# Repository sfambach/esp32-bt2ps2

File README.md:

1/9/24: Serial Mouse support is out for v0.7! Check notes on [release](https://github.com/Hamberthm/esp32-bt2ps2/releases)

24/8/24: Mouse and Multimedia Key support is out for v0.6! Check notes on release

Tested Bluetooth Keyboards and Mice (Please add your own!): [Excel spreadsheet](https://1drv.ms/x/c/496a36eb8f7bab52/EVKre4_rNmoggEllRQIAAAABdvU2lrtNIQN1tRJOs5V3sw?e=jx4JUH)

FreeRTOS ticking rate of 1000hz and other configs are critical. Be sure to use the default SDKconfig.defaults file included!

# ESP32 Bluetooth/BLE to PS/2 keyboard/mouse adapter

## Hardware (this fork)

This fork adds **carrier boards** for the adapter in [`hardware/`](hardware/README.md), each with level shifters and a
4-pin connector for a PS/2 or AT keyboard cable. KiCad 10 files, Gerbers for JLCPCB, schematics and bills of
materials are included.

- **Version 2 (current, [`hardware/v2/`](hardware/v2/README.md)):** SMD board with a soldered-on *ESP32-WROOM-32E*,
  and two through-hole boards, one for a plugged-in *D1 mini ESP32* and one for a soldered-on WROOM; all with
  auto-reset or USB for flashing. **Not manufactured yet.**
- **Version 1 ([`hardware/v1/`](hardware/v1/README.md)):** SMD and THT board, **built and tested**. Gerbers as
  manufactured on the [release v0.1](https://github.com/sfambach/esp32-bt2ps2/releases/tag/v0.1).

| V2 SMD | V2 THT D1 mini | V2 THT WROOM |
|---|---|---|
|  |  |  |

Project to adapt a Bluetooth or BLE keyboard and/or mouse to use on a computer with compatible PS/2 keyboard/mouse connector/s, wirelessly.
Note that big DIN 5 pin connectors ("AT" keyboard) and Mini-DINs (the violet ones) are equally supported.

YouTube demo: https://youtu.be/2PVjWfAAJFE

# Compatibility

Tested Bluetooth Keyboards and Mice (Please add your own!): https://1drv.ms/x/s!AlKre4_rNmpJiYpl1v4KcbK1Pm77zA?e=0I6QRB

Builds with ESP-IDF v5.3.0 and v6.1.0 (both build-tested in this fork; v5.3.3 up to v5.x was reported NOT working upstream and is untested here), compiled on Visual Studio Code. Multi-device support may not work on lower versions of the SDK.

**Developed and tested on the ESP32 DevKit rev 1 board, other variants may not work!**

WARNING: This project is for use in a plain ESP-32 module with BLE and BT Classic support and dual core processor. If you have another variant like C3, you'll have to adapt the code.

* ESP32 S3/C3 (BLE only boards): Check https://github.com/Hamberthm/esp32-bt2ps2/issues/3
* USB-HID instead of PS/2: Check https://github.com/Hamberthm/esp32-bt2ps2/issues/4

# Electrical connections

DIN and Mini-DIN connectors have similar pinout but in different arrangements.

Please use a multimeter and online info to make your cable. Beware of voltage present on the port, you can short and fry things!

Connections:

| ESP32 pin | PS/2 pin | example color | Notes                              |
| --------- | -------- | ------------- |  --------------------------------- |
| 23 or any | DATA     | orange        | Repeat on other pin for mouse bus  |
| 22 or any | CLK      | white         | Repeat on other pin for mouse bus  |
| GND       | GND      | black         | Always connect!                    |
| Vin       | +5v      | red           | Disconnect if using USB power!     |

You can change the DATA and CLK pins to whatever suits your fancy using these lines in the main.cpp file:

```cpp
const int KB_CLK_PIN = 22;
const int KB_DATA_PIN = 23;

const int MOUSE_CLK_PIN = 26;
const int MOUSE_DATA_PIN = 25;
```
Note: Pin 12 & 13 are ideal to solder a connector so you can use Vin, GND, 13 and 12 all in a row (ESP32 DevKit rev 1 boards). BEWARE that pin 12 is a strapping pin on the ESP32 and the module will FAIL to boot due to high signals from the PS/2 port. You can remove the strapping function of pin 12 by blowing an [eFuse](https://docs.espressif.com/projects/esptool/en/latest/esp32s2/espefuse/index.html) on your board. Use the following command:

```
python espefuse.py --port COM4 set_flash_voltage 3.3V
```

Also, applying voltage to pins 1 & 3 (U0 TXD and RXD) could cause the serial communication not to work, thus making serial console output impossible. Be careful on the ones you choose!

There is no need to connect the 5 volts from the port if you wish to power the board over USB. For debugging I recommend you leave it disconnected, as you can end up back-feeding 5 volts back to the PS/2 port, bad things can happen. Once all is working and you don't want to debug anymore, the 5 volts from the port are enough to power the board over the Vin (regulated) pin, making this a pretty neat standalone device!

NOTE: Don't leave the GND cable from the PS2 port floating, otherwise communication won't work! Always connect GND cable to the board even if you're using external power.

Note: ESP32 is **unofficially** 5V tolerant, so you can directly connect PS/2 pins to the board, that's my setup on my rev v1 board and I had no problems. However, you may use a logic level converter.

# Building and flashing

*Note there's a binary release available!

Project works as-is under Visual Studio Code (2024). You need to have the Espressif IDF extension installed and ESP-IDF v5.3.0 or v6.1.0 (build-tested). Workflow is as follows:

1- Install Visual Studio Code

2- On the left, open the extensions panel

3- Search and install the Espressif IDF extension

4- Open the command prompt pressing Ctrl+Shift+P

5- Execute command "ESP-IDF: Configure ESP-IDF extension"

6- Select Express, and under "Select ESP-IDF version" choose v5.3.0 or v6.1.0 (v5.3.3 up to v5.x reported NOT working upstream, untested here)

7- After installation, select File > Open Folder and open the ESP32-BT2PS2 project folder

8- Start building by pressing Ctrl+E and then B, or using the Build button in the bottom bar

9- If succesfully built, connect and flash your ESP32 board (Ctrl+E then F, or the flash button)

Or on the command line (Linux; on Windows use the ESP-IDF installer and `idf.py` in its shell):

```
git clone -b v6.1.0 --recursive https://github.com/espressif/esp-idf.git
cd esp-idf && ./install.sh esp32 && . ./export.sh
git clone https://github.com/sfambach/esp32-bt2ps2.git
cd esp32-bt2ps2 && idf.py build
idf.py -p /dev/ttyUSB0 -b 115200 flash monitor
```

Keep the committed `sdkconfig` (1000 Hz FreeRTOS tick, BLE 4.2 API enabled).

Refer to the following link for more instructions:

* https://github.com/espressif/vscode-esp-idf-extension/blob/master/docs/tutorial/install.md

Once succesfully built and flashed, you're ready to rock! (your BLE keyboard on an ancient computer, that is).

## Known problems (this fork)

**Build failed with ESP-IDF 6.x (fixed).** The linker reported `undefined reference to 'esp_ble_gap_set_scan_params'`, `esp_ble_gap_start_scanning` and `esp_ble_resolve_adv_data`, because the old committed sdkconfig (from v5.3.0) had the legacy BLE 4.2 API disabled. `sdkconfig.defaults` now sets `CONFIG_BT_BLE_42_FEATURES_SUPPORTED=y` and `CONFIG_BT_BLE_42_SCAN_EN=y`, and `sdkconfig` was regenerated with v6.1.0. Build-tested with ESP-IDF v6.1.0 and v5.3.0 (`idf.py fullclean build`); the v6.1 build runs on hardware (ESP32 DevKit, Micro 8088).

**AltGr unreliable, swallowed keys and stuck modifiers on slow hosts (fixed).** Seen on a Micro 8088 (Sergey Kiselev) with DOS 3.31 and KEYB GR, while a real PS/2 keyboard worked. The PS/2 sender in `esp32-ps2dev` dropped the rest of a packet when the host held CLK low for more than 1.5 ms after a byte (e.g. while INT 9 processed `E0`), did not notice when the host aborted a byte mid-transfer, answered Resend (`FE`) with `FA` instead of repeating the last byte, and gave up on a packet when the host wanted to send a command. Lost `E0` bytes turned AltGr into left Alt, and lost break codes left Ctrl/Alt stuck. Now each byte is retried (up to 100 ms) and retransmitted after a host abort or command, Resend repeats the last byte, and there is a 1 ms gap between bytes of a packet (as in HIDman).

**`#` and `<>` missing on German/ISO keyboards.** The ISO keys Non-US # (HID 0x32) and Non-US \ (HID 0x64) had no PS/2 mapping and were dropped. Fixed in this fork (#2): 0x32 sends set-2 code 0x5D, 0x64 sends 0x61.

**Slow BLE reconnect (fixed).** After the keyboard woke up or came back in range it took several seconds to type again. The BLE connection daemon always ran its full 5 s scan before looking for the bonded keyboard, and every reconnect re-read the keyboard's GATT database (`CONFIG_BT_GATTC_CACHE_NVS_FLASH` was off). Now the daemon stops the scan as soon as a bonded device advertises and connects right away, and the GATT cache is on. A monitor log from 31.10.2026 showed the same delay after power-on: the startup pairing scan saw the keyboard at 11.7 s but connected only at 21.7 s, after finishing the 5 s BLE scan and the 5 s BT Classic inquiry. The startup scan now also stops early for a bonded keyboard and skips the BT Classic inquiry then. Confirmed on hardware (01.11.2026, RK-M75 BLE): connected about 1.1 s after the keyboard starts advertising, both after power-on and after the keyboard dropped the link.

# Usage and debugging

Once powered up and first of all, the code will create and init an `esp32_ps2dev::PS2Keyboard` object, so it can start to talk to the computer as soon as possible. This is critical because during boot the BIOS can send different commands to the module to test the presence of the keyboard.

After PS/2 init, the module scans for nearby Bluetooth and BLE devices. If the last bonded keyboard is in range, it will try to connect to it using the keys stored on the NVS flash, so no pairing is needed for every connection. If it doesn't detect a previously bonded device, it will try to connect to the nearest keyboard in pairing mode. If both processes fail, it will wait one second and scan again until it finds anything.

IMPORTANT: Is recommended to do the pairing to the keyboard BEFORE connecing the board to a PS/2 port. For this, connect a charger or power bank to the ESP's USB port and pair your device more comfortably.

For v0.6, you can invoke pairing during execution (blue LED on) at any time. Press the "BOOT" button on the rev v1 board, essentially shorting GPIO_0 to ground. LED will go off and enter pairing mode. To cancel pairing, press and hold for 3 seconds (pairing aborting does not work on startup pairing).

**LED off: Pairing mode activated. LED on: normal execution, only previously paired devices can connect at any time.**

### >> BLE KEYBOARD OR MOUSE PAIRING: 
Set keyboard or mouse in pairing mode and power on the board. No code entry required.

### >> BLUETOOTH CLASSIC KEYBOARD PAIRING (code pairing):

1- Set keyboard in pairing mode and power on the board.

2- Wait until you see a short blast of quick flashes, then pay attention:

3- For each code digit, the board will flash the LED the number of times equal to the digit.

4- Press each digit on the keyboard as you read them (do not wait until it finishes! Some keyboards have a timeout).

5- If the digit is 0, a steady light will show for 1.5 seconds instead of the digit.

6- When you see the blast of quick flashes again, press ENTER.

OR you can always look at the code using the Serial monitor console, whatever you find easier, you fancy boy.

### >> BLUETOOTH CLASSIC KEYBOARD PAIRING, LEGACY PROCEDURE (legacy code pairing):

In older keyboards, the user must enter a custom code on the host device and then on the keyboard. Since we can't input it easily on the ESP32, the code is fixed to 1234.

1- Set keyboard in pairing mode and power on the board

2- Watch the Serial Ouput Console. Wait for the board finishing the scan and for the message "Waiting pairing code entry..."

3- Type 1234 on the keyboard then press ENTER.

Note: For Legacy Mode, no LED output is possible at the moment, so we need to check the serial console for the right time to enter the code. 

---

- If paired and working correctly, the board should blink the LED with each key press on the keyboard, or with each click on the mouse

Once connected you can start using your keyboard and mouse, blue LED should be on. Remove any USB power source and connect the board to the PS/2 compatible system and enjoy. Remember PS/2 is NOT a HOT-SWAP protocol, please only connect the board with the system totally OFF.

You can hot-disconnect the keyboard and mouse for models that support multiple devices hopping. The module will detect the disconnection and repeatedly try to reconnect while you're using other systems, so it will be back online as soon as the keyboard gets up to the ESP32 again. This is critical for keyboards/mouses that go to sleep and disconnect, or if you swap between computers using a multi-connection keyboard. 

Please note that pairing is only done after power up. If you wish to pair a new device, please reset the module with the reset button or power off and on the computer (not just reset it, because we need a power cycle). Note that if a previously paired device is on and in range, it will always connect to it first. Also invoke pairing after power on (LED on) by using the BOOT button or shorting GPIO_0 to ground.

In case something doesn't work, you'll need to debug. 

If the blue light on the module lights up and your keyboard connects, but it doesn't work, first of all reset your system. If it still doesn't work, then you'll need to enable debugging in the `esp32-ps2dev.cpp` file using `#DEFINE _ESP32_PS2DEV_DEBUG_`. Check for "PS/2 command received" messages and see where it hangs, or what the BIOS doesn't like. This is advanced so if you need help, make a new issue.

# TODO
 * Test on many keyboards and mouses.
 * Improve stability.
 * Clean up the code.
 * Test against various hosts.

# Reference
- http://www-ug.eecg.toronto.edu/msl/nios_devices/datasheets/PS2%20Protocol.htm
- http://www-ug.eecg.toronto.edu/msl/nios_devices/datasheets/PS2%20Mouse%20Protocol.htm
- http://www-ug.eecg.toronto.edu/msl/nios_devices/datasheets/PS2%20Keyboard%20Protocol.htm

# History
Using code and hard work from these folks:
 
 * https://playground.arduino.cc/ComponentLib/Ps2mouse/
 * https://github.com/grappendorf/arduino-framework/tree/master/ps2dev
 * https://github.com/dpavlin/Arduino-projects/tree/master/libraries/ps2dev
 * ps2 library Written by Chris J. Kiick, January 2008. https://github.com/ckiick
 * modified by Gene E. Scogin, August 2008.
 * modified by Tomas 'Harvie' Mudrunka 2019. https://github.com/harvie/ps2dev
 * modified for ESP32 by hrko 2022. https://github.com/hrko/esp32-ps2dev
 * fixed for PC compatibility and stability by Hambert, 2023. https://github.com/Hamberthm/esp32-ps2dev
 * bt-keyboard library by Guy Turcotte, 2022. https://github.com/turgu1/bt-keyboard
 * adapted to Arduino IDE and added improvements by Hambert, 2023. https://github.com/Hamberthm/bt-keyboard

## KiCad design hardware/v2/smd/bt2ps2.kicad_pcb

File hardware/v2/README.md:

# Version 2 (current)

> ⚠️ **Not manufactured yet.** Designed and checked (ERC/DRC clean), routed with Freerouting. Replaces
> [version 1](../v1/README.md) once built and tested.

What changed against V1:
- **SMD (2026-10-31):** the D1 mini socket is gone, the WROOM is rotated 90° (antenna over the left edge), all parts
  are on the front, 49 × 31 mm instead of 61 × 34 mm. J3 has 6 pins with DTR/RTS auto-reset (Q3/Q4, MMBT3904).
- **THT (2026-11-01):** the combined board is split in two. **D1 mini:** socket, level shifter, J1/JP1 only
  (regulator, reset and BOOT are on the D1 mini). **WROOM:** the LD1117V33 lies flat (TO-220 horizontal, about
  4.5 mm instead of 15 mm high) and J3 has 6 pins with auto-reset (BC547). Two M3 holes on the long axis.
- LED anode marked with `+`, J3 pins labelled on the silkscreen.

## SMD

## THT

| D1 mini | WROOM |
|---|---|
|  |  |
|  |  |

Bills of materials: [SMD](smd/fertigung/stueckliste.csv), [THT D1 mini](tht-d1/fertigung/stueckliste.csv),
[THT WROOM](tht-wroom/fertigung/stueckliste.csv). Enclosures: [`../case/`](../case/README.md) (`smd`, `tht-d1`, `tht-wroom`).

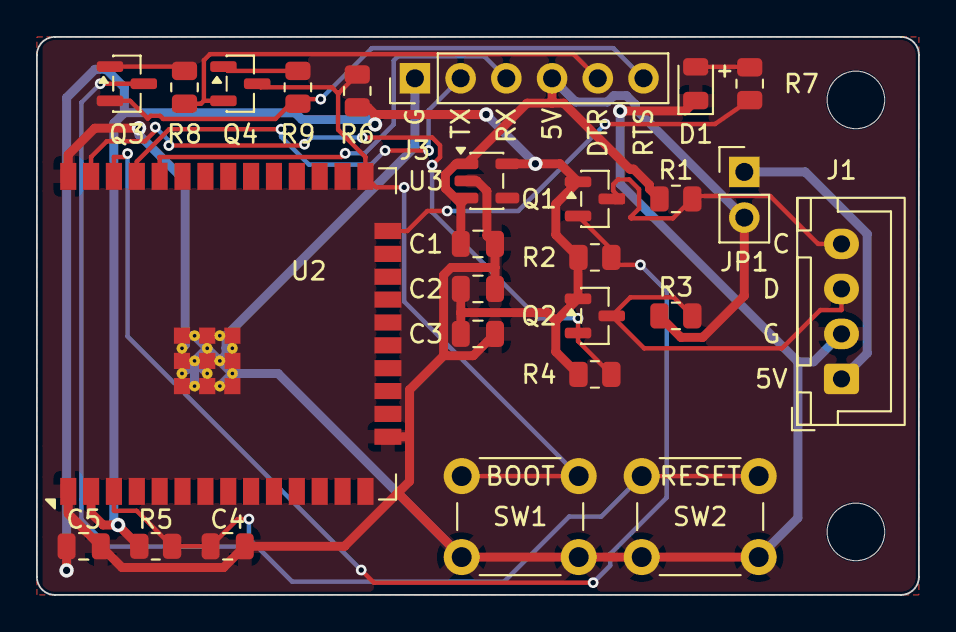
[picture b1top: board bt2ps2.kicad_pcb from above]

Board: 2 copper layers, 49.0 x 31.0 mm, 28 parts (0 on the bottom side), 18 nets.

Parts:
C1, C2: 10u; C_0805_2012Metric
C3, C5: 100n; C_0805_2012Metric
C4: 1u; C_0805_2012Metric
D1: blau; LED_0805_2012Metric
H1, H2: M3; MountingHole_3.2mm_M3
J1: PS2_Tastatur; JST_XH_B4B-XH-A_1x04_P2.50mm_Vertical
J3: Programmer; PinHeader_1x06_P2.54mm_Vertical
JP1: 5V_vom_PC; PinHeader_1x02_P2.54mm_Vertical
Q1, Q2: BSS138; SOT-23
Q3, Q4: MMBT3904; SOT-23
R1, R2, R3, R4, R5, R6, R8, R9: 10k; R_0805_2012Metric
R7: 1k; R_0805_2012Metric
SW1: BOOT; SW_PUSH_6mm
SW2: RESET; SW_PUSH_6mm
U2: ESP32-WROOM-32E-N4; ESP32-WROOM-32E
U3: AP2112K-3.3; SOT-23-5

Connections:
+3V3: C2.1, C3.1, C5.1, Q1.1, Q2.1, R2.1, R4.1, R5.1, R6.1, U2.2, U3.5
+5V: C1.1, J3.4, JP1.2, R1.1, R3.1, U3.1, U3.3
/+5V_PC: J1.1, JP1.1
/BOOT: Q4.3, R6.2, SW1.1, U2.25
/DTR: J3.5, Q4.2, R8.1
/EN: C4.1, Q3.3, R5.2, SW2.1, U2.3
/ESP_RXD: J3.3, U2.34
/ESP_TXD: J3.2, U2.35
/KB_CLK: Q1.2, R2.2, U2.36
/KB_CLK_5V: J1.4, Q1.3, R1.2
/KB_DATA: Q2.2, R4.2, U2.37
/KB_DATA_5V: J1.3, Q2.3, R3.2
/LED: R7.1, U2.24
/LED_A: D1.2, R7.2
/RTS: J3.6, Q3.2, R9.1
GND: C1.2, C2.2, C3.2, C4.2, C5.2, D1.1, J1.2, J3.1, SW1.2, SW2.2, U2.1, U2.15, U2.38, U2.39, U3.2
unnamed: Q3.1, R8.2
unnamed: Q4.1, R9.2

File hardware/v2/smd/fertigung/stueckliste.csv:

"Bauteile","Wert","Gehaeuse","Anzahl"
"C1,C2","10u","Capacitor_SMD:C_0805_2012Metric","2"
"C3,C5","100n","Capacitor_SMD:C_0805_2012Metric","2"
"C4","1u","Capacitor_SMD:C_0805_2012Metric","1"
"D1","blau","LED_SMD:LED_0805_2012Metric","1"
"J1","PS2_Tastatur","Connector_JST:JST_XH_B4B-XH-A_1x04_P2.50mm_Vertical","1"
"J3","Programmer","Connector_PinHeader_2.54mm:PinHeader_1x06_P2.54mm_Vertical","1"
"JP1","5V_vom_PC","Connector_PinHeader_2.54mm:PinHeader_1x02_P2.54mm_Vertical","1"
"Q1,Q2","BSS138","Package_TO_SOT_SMD:SOT-23","2"
"Q3,Q4","MMBT3904","Package_TO_SOT_SMD:SOT-23","2"
"R1-R6,R8,R9","10k","Resistor_SMD:R_0805_2012Metric","8"
"R7","1k","Resistor_SMD:R_0805_2012Metric","1"
"SW1","BOOT","Button_Switch_THT:SW_PUSH_6mm","1"
"SW2","RESET","Button_Switch_THT:SW_PUSH_6mm","1"
"U2","ESP32-WROOM-32E-N4","RF_Module:ESP32-WROOM-32E","1"
"U3","AP2112K-3.3","Package_TO_SOT_SMD:SOT-23-5","1"

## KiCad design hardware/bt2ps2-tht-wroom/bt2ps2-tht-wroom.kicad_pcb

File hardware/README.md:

# Hardware: carrier boards for esp32-bt2ps2

Boards for the firmware in this repository — **keyboard only**, same pins as the firmware defaults
(`KB_CLK_PIN = 22`, `KB_DATA_PIN = 23`), so the firmware runs unchanged. 2-layer boards for JLCPCB's standard
process (1.6 mm, 1 oz, HASL), designed with **KiCad 10**.

## Versions

| Version | Folder | Boards | Status |
|---|---|---|---|
| **V2 (current)** | [`v2/`](v2/README.md) | SMD, THT D1 mini, THT WROOM | designed, DRC clean, **not manufactured yet** |
| V1 | [`v1/`](v1/README.md) | SMD, THT (D1 mini **or** WROOM on one board) | **built and tested** (both boards run at the PC) |

V2 replaces V1 once it is built and tested. Each board folder holds its own KiCad project, schematic, renders,
bill of materials (`fertigung/stueckliste.csv`) and Gerbers; V1 also has photos of the built boards (`fotos/`).
V1 Gerbers as manufactured: [release v0.1](https://github.com/sfambach/esp32-bt2ps2/releases/tag/v0.1).

| V2 | [SMD](v2/smd) | [THT D1 mini](v2/tht-d1) | [THT WROOM](v2/tht-wroom) |
|---|---|---|---|
| ESP32 | ESP32-WROOM-32E soldered on | D1 mini ESP32 plugged in | ESP32-WROOM-32E soldered on |
| Level shifter 5 V ↔ 3.3 V | 2 × BSS138 (SOT-23) + 10 kΩ | 2 × 2N7000 (TO-92) + 10 kΩ | 2 × 2N7000 (TO-92) + 10 kΩ |
| 3.3 V regulator | AP2112K-3.3 | on the D1 mini | LD1117V33, TO-220 lying flat |
| Programming | J3 with auto-reset | USB of the D1 mini | J3 with auto-reset (2 × BC547) |
| Passives | 0805 | through-hole | through-hole (the WROOM is the only SMD part) |
| Size | 49.0 × 31.0 mm | 60.0 × 34.2 mm | 63.0 × 44.0 mm |

## Enclosures

3D-printable cases for the boards (shell + lid, OpenSCAD source and STLs) are in [`case/`](case/README.md).

## What is on the boards (V1 and V2)

- **J1 – keyboard connector to the PC** (JST-XH, 4 pins): `1 = +5V`, `2 = GND`, `3 = DATA`, `4 = CLK` (printed as
  `5V G D C`). Crimp a cable to a PS/2 (Mini-DIN-6) or AT (DIN-5) plug:

  | J1 | PS/2 Mini-DIN-6 pin | AT DIN-5 pin |
  |---|---|---|
  | 1 +5V | 4 | 5 |
  | 2 GND | 3 | 4 |
  | 3 DATA | 1 | 2 |
  | 4 CLK | 5 | 1 |

  Pinouts as commonly documented — **measure your plug before use.**
- **JP1 – 5 V from the PC.** Pull the jumper while the board is powered over USB (or J3), otherwise 5 V is fed back
  into the PC's keyboard port — the same warning as in the main README.
- **THT D1 mini board:** a *D1 mini ESP32* (MH-ET LIVE MiniKit / "D1 mini ESP32 ESP-WROOM-32", 4 rows of pins,
  39 × 32 mm) on female headers. Programming via its own USB port. Its USB end is flush with the board edge,
  its antenna overhangs the opposite edge.
- **SMD board / THT WROOM board:** an ESP32-WROOM-32E soldered on, antenna over the board edge. Adds the
  3.3 V regulator, EN/BOOT circuitry, **BOOT** and **RESET** buttons, a status LED on IO2 and **J3** for a
  USB-serial adapter: `1 GND`, `2 ESP TXD → adapter RX`, `3 ESP RXD → adapter TX`, `4 +5V`.
  `5 DTR` and `6 RTS` drive the usual two-transistor auto-reset (Q3/Q4, R8/R9, as on the ESP32-DevKitC; SMD
  MMBT3904, THT BC547): an adapter that brings out DTR and RTS flashes without pressing BOOT/RESET. A 4-wire adapter
  on pins 1–4 still works, then hold BOOT, tap RESET, release BOOT. (V1 boards have a 4-pin J3.)
- IO25/IO26 are kept free for the mouse port (planned for version 2).

## Files per board

| File | |
|---|---|
| `*.kicad_pro`, `*.kicad_sch`, `*.kicad_pcb` | KiCad 10 project |
| `*.kicad_dru` | design rules for JLCPCB |
| `*.kicad_sym`, `*.pretty/` | symbol and footprint of the D1 mini ESP32 socket (boards with a D1 mini) |
| `*-schaltplan.pdf` / `.svg` | schematic |
| `fertigung/*-jlcpcb-gerber.zip` | Gerber + drill files, ready to upload to JLCPCB |
| `fertigung/bestueckung-*.pdf` | assembly drawings |
| `fotos/` | photos of the built board (V1) |
| `fertigung/*-ibom.html` | interactive BOM (open in a browser; V1 boards only) |
| `fertigung/stueckliste.csv` | bill of materials |
| `fertigung/*-jlcpcb-positionen.csv` | pick-and-place data, origin at the lower left corner of the board |

## Notes and open points

- **2N7000 at 3.3 V gate (THT boards):** Vgs(th) is typically 2.1 V but may be up to 3 V. It works on the built
  V1 THT board. A BS170 is *not* a drop-in replacement (different pinout).
- The D1 mini footprint is based on [r0oland/ESP32_mini_KiCad_Library](https://github.com/r0oland/ESP32_mini_KiCad_Library)
  and was checked against the pinout of an actual board; the outline and antenna position are estimated (±1 mm).
- **Planned for the next revision: reverse-protection diode in the PC 5 V path.** A Schottky diode (THT 1N5817,
  SMD SS14) from J1 pin 1 to the board's +5 V, in series with JP1, so the board can stay on USB and on the PC at
  the same time without feeding 5 V back into the keyboard port. The ~0.3 V drop is harmless for the 3.3 V regulator
  and the PS/2 pull-ups. WROOM boards: a second diode in the J3 5 V input. D1 mini board: check whether the D1 mini has its
  own diode between USB VBUS and its 5 V pin, otherwise the PC could still feed the USB host. Until then: pull JP1
  while USB is connected.
- **LD1117V33 lying flat:** the tab is the output (3.3 V) and rests on solder mask over the GND pour, which
  insulates it. The tab hole takes an M3 screw if you want it fixed; do not connect it to GND.
- V1 THT board: traces laid out by a simple grid router — functional, not pretty. SMD V2 and the two new
  THT boards: routed with Freerouting; GND runs through the copper pours on both layers.

Designed by Stefan Fambach — [fambach.net](https://www.fambach.net). The hardware in this folder is licensed under the
[MIT License](LICENSE), like the firmware.

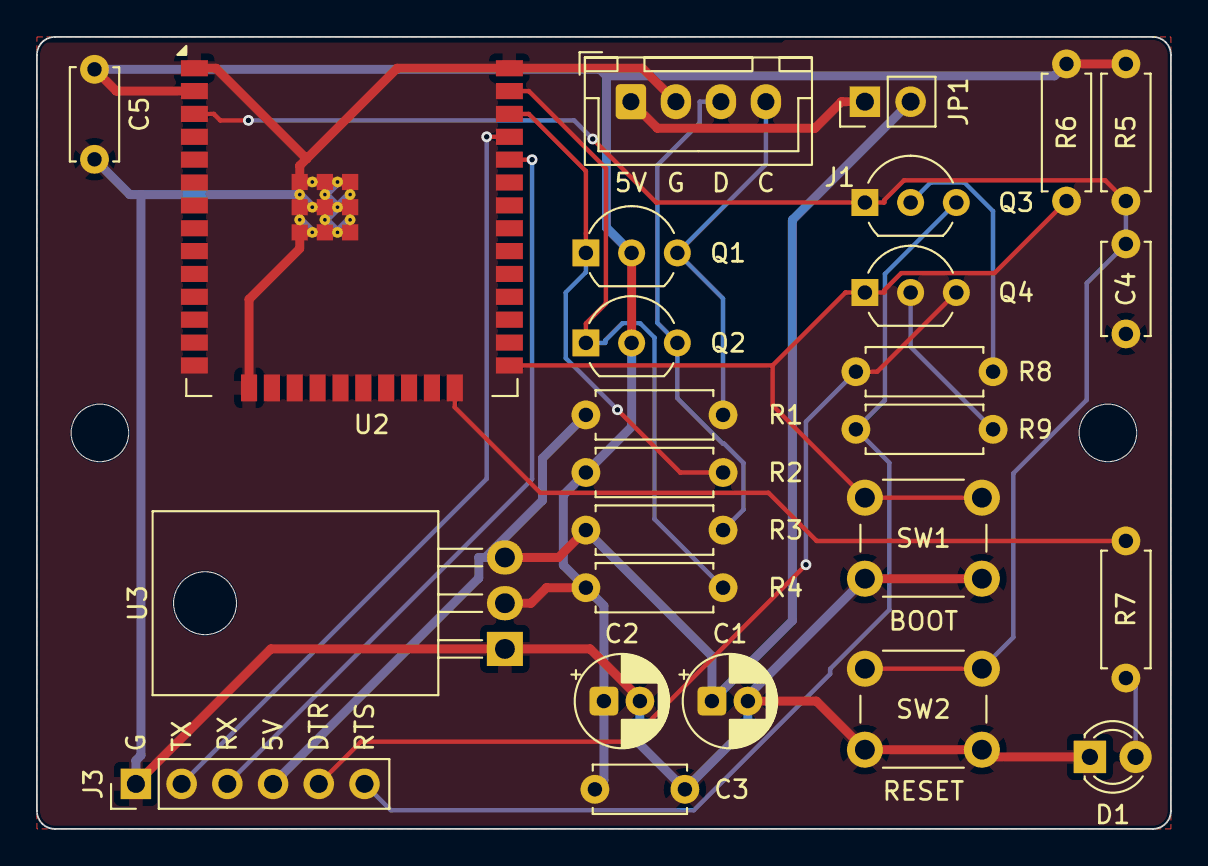
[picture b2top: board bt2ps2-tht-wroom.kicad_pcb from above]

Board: 2 copper layers, 63.0 x 44.0 mm, 28 parts (0 on the bottom side), 18 nets.

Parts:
C1, C2: 10u; CP_Radial_D5.0mm_P2.00mm
C3, C5: 100n; C_Disc_D5.0mm_W2.5mm_P5.00mm
C4: 1u; C_Disc_D5.0mm_W2.5mm_P5.00mm
D1: blau; LED_D3.0mm
H1, H2: M3; MountingHole_3.2mm_M3
J1: PS2_Tastatur; JST_XH_B4B-XH-A_1x04_P2.50mm_Vertical
J3: Programmer; PinHeader_1x06_P2.54mm_Vertical
JP1: 5V_vom_PC; PinHeader_1x02_P2.54mm_Vertical
Q1, Q2: 2N7000; TO-92_Inline_Wide
Q3, Q4: BC547; TO-92_Inline_Wide
R1, R2, R3, R4, R5, R6, R8, R9: 10k; R_Axial_DIN0207_L6.3mm_D2.5mm_P7.62mm_Horizontal
R7: 1k; R_Axial_DIN0207_L6.3mm_D2.5mm_P7.62mm_Horizontal
SW1: BOOT; SW_PUSH_6mm
SW2: RESET; SW_PUSH_6mm
U2: ESP32-WROOM-32E-N4; ESP32-WROOM-32E
U3: LD1117V33; TO-220-3_Horizontal_TabDown

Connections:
+3V3: C2.1, C3.1, C5.1, Q1.2, Q2.2, R2.1, R4.1, R5.1, R6.1, U2.2, U3.2
+5V: C1.1, J3.4, JP1.2, R1.1, R3.1, U3.3
/+5V_PC: J1.1, JP1.1
/BOOT: Q4.1, R6.2, SW1.1, U2.25
/DTR: J3.5, Q4.3, R8.1
/EN: C4.1, Q3.1, R5.2, SW2.1, U2.3
/ESP_RXD: J3.3, U2.34
/ESP_TXD: J3.2, U2.35
/KB_CLK: Q1.1, R2.2, U2.36
/KB_CLK_5V: J1.4, Q1.3, R1.2
/KB_DATA: Q2.1, R4.2, U2.37
/KB_DATA_5V: J1.3, Q2.3, R3.2
/LED: R7.1, U2.24
/LED_A: D1.2, R7.2
/RTS: J3.6, Q3.3, R9.1
GND: C1.2, C2.2, C3.2, C4.2, C5.2, D1.1, J1.2, J3.1, SW1.2, SW2.2, U2.1, U2.15, U2.38, U2.39, U3.1
unnamed: Q3.2, R8.2
unnamed: Q4.2, R9.2

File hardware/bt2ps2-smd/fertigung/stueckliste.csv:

"Bauteile","Wert","Gehaeuse","Anzahl"
"C1,C2","10u","Capacitor_SMD:C_0805_2012Metric","2"
"C3,C5","100n","Capacitor_SMD:C_0805_2012Metric","2"
"C4","1u","Capacitor_SMD:C_0805_2012Metric","1"
"D1","blau","LED_SMD:LED_0805_2012Metric","1"
"J1","PS2_Tastatur","Connector_JST:JST_XH_B4B-XH-A_1x04_P2.50mm_Vertical","1"
"J3","Programmer","Connector_PinHeader_2.54mm:PinHeader_1x04_P2.54mm_Vertical","1"
"JP1","5V_vom_PC","Connector_PinHeader_2.54mm:PinHeader_1x02_P2.54mm_Vertical","1"
"Q1,Q2","BSS138","Package_TO_SOT_SMD:SOT-23","2"
"R1-R6","10k","Resistor_SMD:R_0805_2012Metric","6"
"R7","1k","Resistor_SMD:R_0805_2012Metric","1"
"SW1","BOOT","Button_Switch_THT:SW_PUSH_6mm","1"
"SW2","RESET","Button_Switch_THT:SW_PUSH_6mm","1"
"U2","ESP32-WROOM-32E-N4","RF_Module:ESP32-WROOM-32E","1"
"U3","AP2112K-3.3","Package_TO_SOT_SMD:SOT-23-5","1"

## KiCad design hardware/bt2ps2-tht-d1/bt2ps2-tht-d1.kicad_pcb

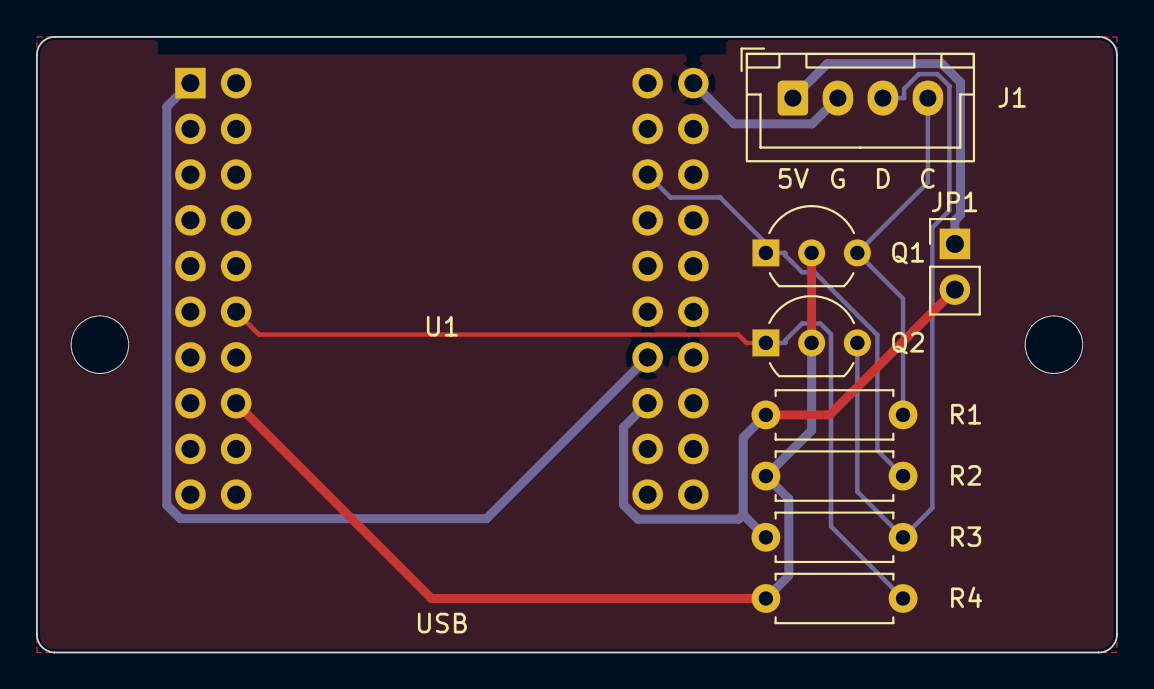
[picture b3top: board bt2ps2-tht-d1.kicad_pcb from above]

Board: 2 copper layers, 60.0 x 34.2 mm, 11 parts (0 on the bottom side), 8 nets.

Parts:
H1, H2: M3; MountingHole_3.2mm_M3
J1: PS2_Tastatur; JST_XH_B4B-XH-A_1x04_P2.50mm_Vertical
JP1: 5V_vom_PC; PinHeader_1x02_P2.54mm_Vertical
Q1, Q2: 2N7000; TO-92_Inline_Wide
R1, R2, R3, R4: 10k; R_Axial_DIN0207_L6.3mm_D2.5mm_P7.62mm_Horizontal
U1: D1_mini_ESP32; D1_mini_ESP32_Sockel

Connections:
+3V3: Q1.2, Q2.2, R2.1, R4.1, U1.16
+5V: JP1.2, R1.1, R3.1, U1.35
/+5V_PC: J1.1, JP1.1
/KB_CLK: Q1.1, R2.2, U1.25
/KB_CLK_5V: J1.4, Q1.3, R1.2
/KB_DATA: Q2.1, R4.2, U1.12
/KB_DATA_5V: J1.3, Q2.3, R3.2
GND: J1.2, U1.1, U1.22, U1.33
